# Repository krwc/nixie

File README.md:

# Another Nixie Clock, because why not?

When my journey into the world of electronics started, a friend of mine has shown me the
beautiful creations capable of presenting time using cold cathode tubes. Ever since then,
I wanted to create something similar, as it seemed like a pretty cool thing to do!

After some time, and two PCB revisions, the clock was actually useful, wasn't exploding,
and was looking quite neat overall to me.

# Safety

- The high voltage trace clearance is enforced to be 0.4mm
- There's a 1A slow fuse on the input
- There's a slow start mechanism implemented on the input, preventing high transient
  current during startup

Anyway, if you intend to use it, please do it on your own risk. Keep in mind, I'm not
a professional PCB designer, nor have a proper electrical education background.

# Acknolwedgements

- The power supply design is based on https://threeneurons.wordpress.com/nixie-power-supply/,
  and the datasheet of MC33063 itself. It is integrated into the main PCB.

- Wemos KiCad model was found somewhere on the internet, unfortunately I can't remember where
  exactly.

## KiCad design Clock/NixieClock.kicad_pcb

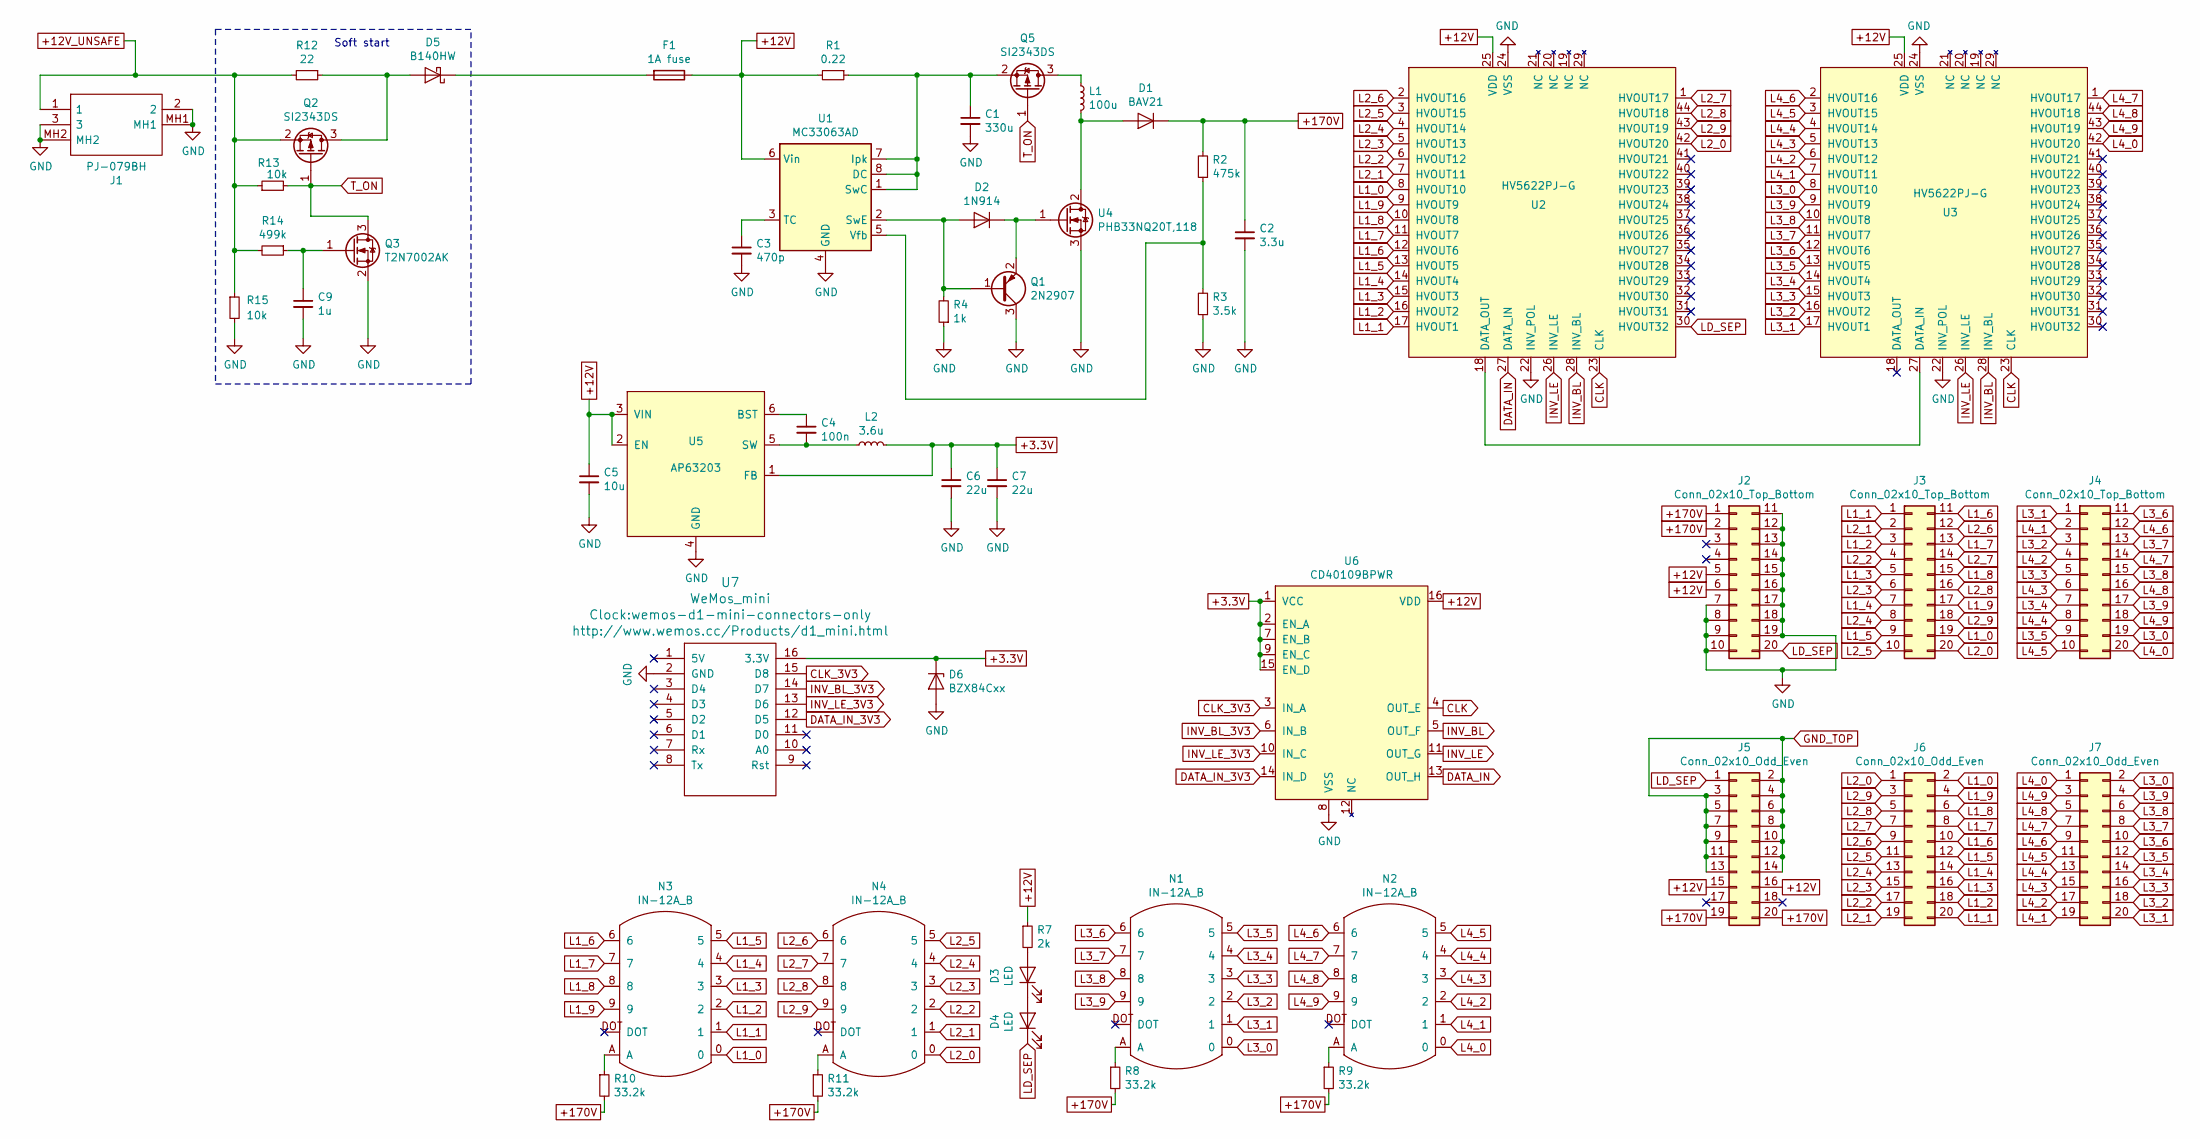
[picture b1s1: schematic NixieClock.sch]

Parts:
C1: 330u; C_Radial_D10.0mm_H20.0mm_P5.00mm
C2: 3.3u; C_Radial_D6.3mm_H11.0mm_P2.50mm
C3: 470p; C_0603_1608Metric
C4: 100n; C_0603_1608Metric_Pad1.05x0.95mm_HandSolder
C5: 10u; C_0805_2012Metric_Pad1.15x1.40mm_HandSolder
C6, C7: 22u; C_0805_2012Metric_Pad1.15x1.40mm_HandSolder
C9: 1u; C_0603_1608Metric_Pad1.05x0.95mm_HandSolder
D1: BAV21; D_SOD-323_HandSoldering
D2: 1N914; D_SOD-323_HandSoldering
D3, D4: LED; LED_D5.0mm_Clear
D5: B140HW; D_SOD-123
D6: BZX84Cxx; D_SOT-23_ANK
F1: 1A fuse; Fuse_1206_3216Metric_Pad1.42x1.75mm_HandSolder
J1: PJ-079BH; PJ079BH
J2, J3, J4: Conn_02x10_Top_Bottom; PinHeader_2x10_P2.54mm_Vertical
J5, J6, J7: Conn_02x10_Odd_Even; PinSocket_2x10_P2.54mm_Horizontal
L1: 100u; L_Bourns_SRR1210A
L2: 3.6u; SRN5040
N1, N2, N3, N4: IN-12A_B; IN12-A_B
Q1: 2N2907; SOT-23_Handsoldering
Q2, Q5: SI2343DS; SOT-23_Handsoldering
Q3: T2N7002AK; SOT-23_Handsoldering
R1: 0.22; R_1210_3225Metric_Pad1.42x2.65mm_HandSolder
R2: 475k; R_1206_3216Metric_Pad1.42x1.75mm_HandSolder
R3: 3.5k; R_1206_3216Metric_Pad1.42x1.75mm_HandSolder
R4: 1k; R_0603_1608Metric_Pad1.05x0.95mm_HandSolder
R7: 2k; R_0603_1608Metric_Pad1.05x0.95mm_HandSolder
R8, R9, R10, R11: 33.2k; R_1206_3216Metric_Pad1.42x1.75mm_HandSolder
R12: 22; R_2512_6332Metric_Pad1.52x3.35mm_HandSolder
R13, R15: 10k; R_0603_1608Metric_Pad1.05x0.95mm_HandSolder
R14: 499k; R_0603_1608Metric_Pad1.05x0.95mm_HandSolder
U1: MC33063AD; SOIC-8_3.9x4.9mm_P1.27mm
U2, U3: HV5622PJ-G; PLCC-44
U4: PHB33NQ20T,118; TO-263-3_TabPin2
U5: AP63203; TSOT-23-6
U6: CD40109BPWR; TSSOP-16_4.4x5mm_P0.65mm
U7: WeMos_mini; wemos-d1-mini-connectors-only

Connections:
+3.3V: C6.1, C7.1, D6.1 (K), L2.2, U5.1 (FB), U6.1 (VCC), U6.2 (EN_A), U6.7 (EN_B), U6.9 (EN_C), U6.15 (EN_D), U7.16 (3.3V)
+12V: C5.1, F1.1, J2.5, J2.6, J5.15, J5.16, R1.2, R7.1, U1.6 (Vin), U2.25 (VDD), U3.25 (VDD), U5.2 (EN), U5.3 (VIN), U6.16 (VDD)
+12V_UNSAFE: J1.1, Q2.2 (S), R12.2, R13.1, R14.2, R15.1
+170V: C2.1, D1.1 (K), J2.1, J2.2, J5.19, J5.20, R2.2, R8.2, R9.2, R10.2, R11.2
CLK: U2.23 (CLK), U3.23 (CLK), U6.4 (OUT_E)
CLK_3V3: U6.3 (IN_A), U7.15 (D8)
DATA_IN: U2.27 (DATA_IN), U6.13 (OUT_H)
DATA_IN_3V3: U6.14 (IN_D), U7.12 (D5)
GND: C1.2, C2.2, C3.2, C5.2, C6.2, C7.2, C9.2, D6.2 (A), J1.2, J1.3, J1.MH1, J1.MH2, J2.7, J2.8, J2.9, J2.10, J2.11, J2.12, J2.13, J2.14, J2.15, J2.16, J2.17, J2.18, J2.19, Q1.3 (C), Q3.2 (S), R3.1, R4.1, R15.2, U1.4 (GND), U2.22 (INV_POL), U2.24 (VSS), U3.22 (INV_POL), U3.24 (VSS), U4.3 (S), U5.4 (GND), U6.8 (VSS), U7.2 (GND)
GND_TOP: J5.2, J5.3, J5.4, J5.5, J5.6, J5.7, J5.8, J5.9, J5.10, J5.11, J5.12, J5.13, J5.14
INV_BL: U2.28 (INV_BL), U3.28 (INV_BL), U6.5 (OUT_F)
INV_BL_3V3: U6.6 (IN_B), U7.14 (D7)
INV_LE: U2.26 (INV_LE), U3.26 (INV_LE), U6.11 (OUT_G)
INV_LE_3V3: U6.10 (IN_C), U7.13 (D6)
L1_0: J3.19, J6.2, N3.0, U2.8 (HVOUT10)
L1_1: J3.1, J6.20, N3.1, U2.17 (HVOUT1)
L1_2: J3.3, J6.18, N3.2, U2.16 (HVOUT2)
L1_3: J3.5, J6.16, N3.3, U2.15 (HVOUT3)
L1_4: J3.7, J6.14, N3.4, U2.14 (HVOUT4)
L1_5: J3.9, J6.12, N3.5, U2.13 (HVOUT5)
L1_6: J3.11, J6.10, N3.6, U2.12 (HVOUT6)
L1_7: J3.13, J6.8, N3.7, U2.11 (HVOUT7)
L1_8: J3.15, J6.6, N3.8, U2.10 (HVOUT8)
L1_9: J3.17, J6.4, N3.9, U2.9 (HVOUT9)
L2_0: J3.20, J6.1, N4.0, U2.42 (HVOUT20)
L2_1: J3.2, J6.19, N4.1, U2.7 (HVOUT11)
L2_2: J3.4, J6.17, N4.2, U2.6 (HVOUT12)
L2_3: J3.6, J6.15, N4.3, U2.5 (HVOUT13)
L2_4: J3.8, J6.13, N4.4, U2.4 (HVOUT14)
L2_5: J3.10, J6.11, N4.5, U2.3 (HVOUT15)
L2_6: J3.12, J6.9, N4.6, U2.2 (HVOUT16)
L2_7: J3.14, J6.7, N4.7, U2.1 (HVOUT17)
L2_8: J3.16, J6.5, N4.8, U2.44 (HVOUT18)
L2_9: J3.18, J6.3, N4.9, U2.43 (HVOUT19)
L3_0: J4.19, J7.2, N1.0, U3.8 (HVOUT10)
L3_1: J4.1, J7.20, N1.1, U3.17 (HVOUT1)
L3_2: J4.3, J7.18, N1.2, U3.16 (HVOUT2)
L3_3: J4.5, J7.16, N1.3, U3.15 (HVOUT3)
L3_4: J4.7, J7.14, N1.4, U3.14 (HVOUT4)
L3_5: J4.9, J7.12, N1.5, U3.13 (HVOUT5)
L3_6: J4.11, J7.10, N1.6, U3.12 (HVOUT6)
L3_7: J4.13, J7.8, N1.7, U3.11 (HVOUT7)
L3_8: J4.15, J7.6, N1.8, U3.10 (HVOUT8)
L3_9: J4.17, J7.4, N1.9, U3.9 (HVOUT9)
L4_0: J4.20, J7.1, N2.0, U3.42 (HVOUT20)
L4_1: J4.2, J7.19, N2.1, U3.7 (HVOUT11)
L4_2: J4.4, J7.17, N2.2, U3.6 (HVOUT12)
L4_3: J4.6, J7.15, N2.3, U3.5 (HVOUT13)
L4_4: J4.8, J7.13, N2.4, U3.4 (HVOUT14)
L4_5: J4.10, J7.11, N2.5, U3.3 (HVOUT15)
L4_6: J4.12, J7.9, N2.6, U3.2 (HVOUT16)
L4_7: J4.14, J7.7, N2.7, U3.1 (HVOUT17)
L4_8: J4.16, J7.5, N2.8, U3.44 (HVOUT18)
L4_9: J4.18, J7.3, N2.9, U3.43 (HVOUT19)
LD_SEP: D4.1 (K), J2.20, J5.1, U2.30 (HVOUT32)
unnamed: C1.1, Q5.2 (S), R1.1, U1.1 (SwC), U1.7 (Ipk), U1.8 (DC)
unnamed: C3.1, U1.3 (TC)
unnamed: C4.1, U5.6 (BST)
unnamed: C4.2, L2.1, U5.5 (SW)
unnamed: C9.1, Q3.1 (G), R14.1
unnamed: D1.2 (A), L1.2, U4.2 (D)
unnamed: D2.1 (K), Q1.2 (E), U4.1 (G)
unnamed: D2.2 (A), Q1.1 (B), R4.2, U1.2 (SwE)
unnamed: D3.1 (K), D4.2 (A)
unnamed: D3.2 (A), R7.2
unnamed: D5.1 (K), F1.2
unnamed: D5.2 (A), Q2.3 (D), R12.1
unnamed: L1.1, Q5.3 (D)
unnamed: N1.A, R8.1
unnamed: N2.A, R9.1
unnamed: N3.A, R10.1
unnamed: N4.A, R11.1
unnamed: R2.1, R3.2, U1.5 (Vfb)
unnamed: U2.18 (DATA_OUT), U3.27 (DATA_IN)
T_ON: Q2.1 (G), Q3.3 (D), Q5.1 (G), R13.2

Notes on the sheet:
Soft start

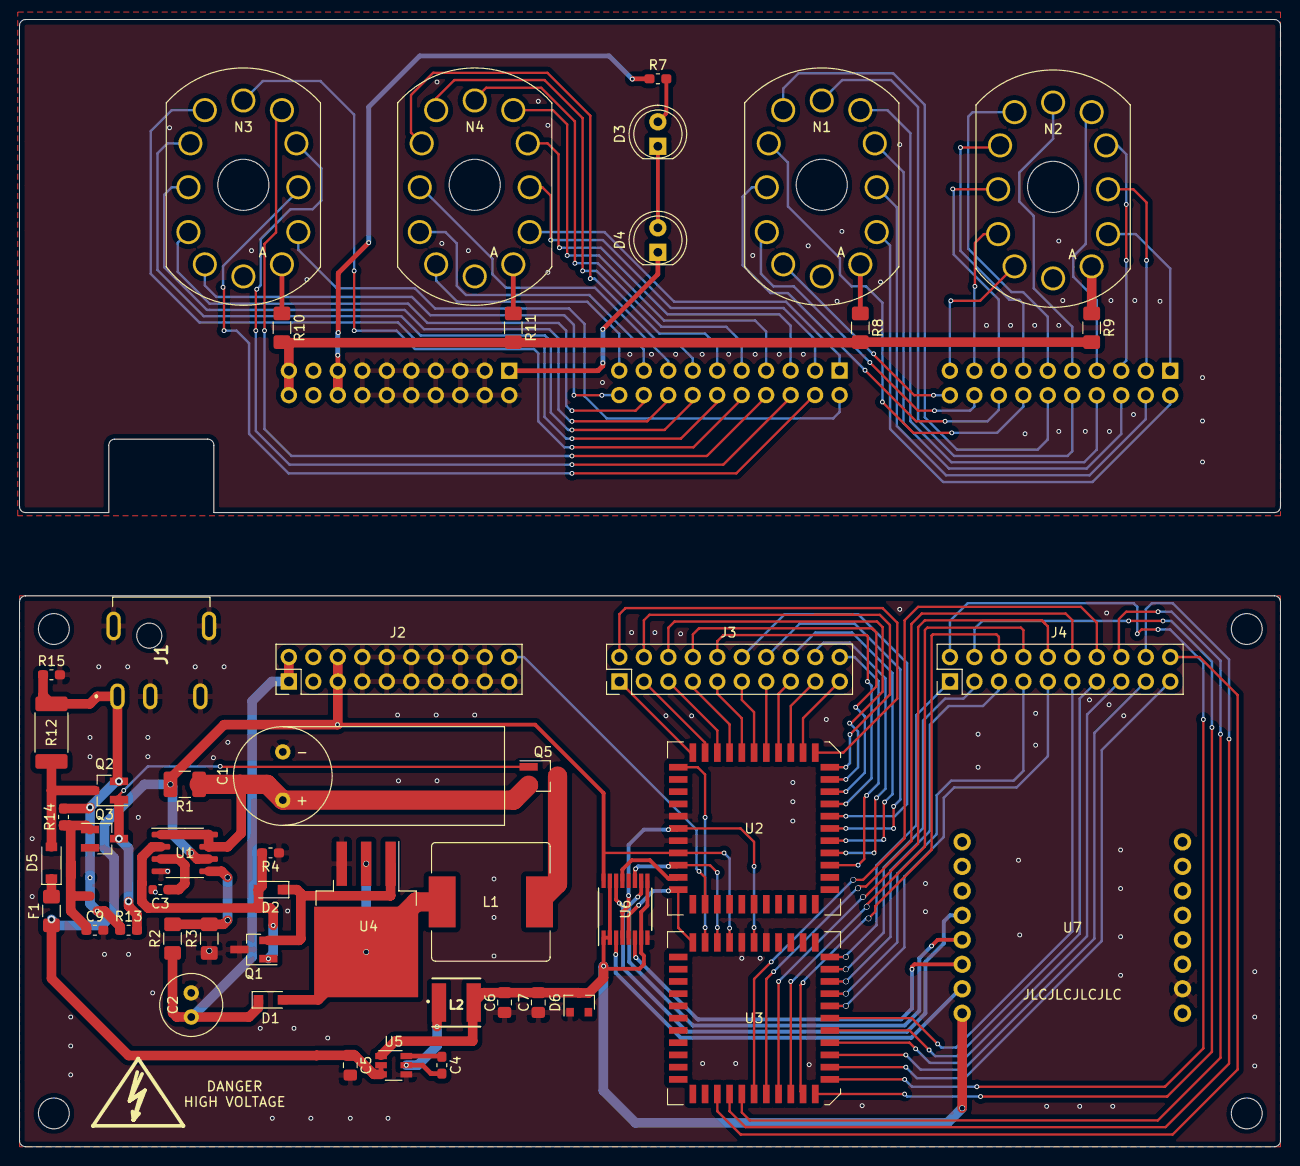
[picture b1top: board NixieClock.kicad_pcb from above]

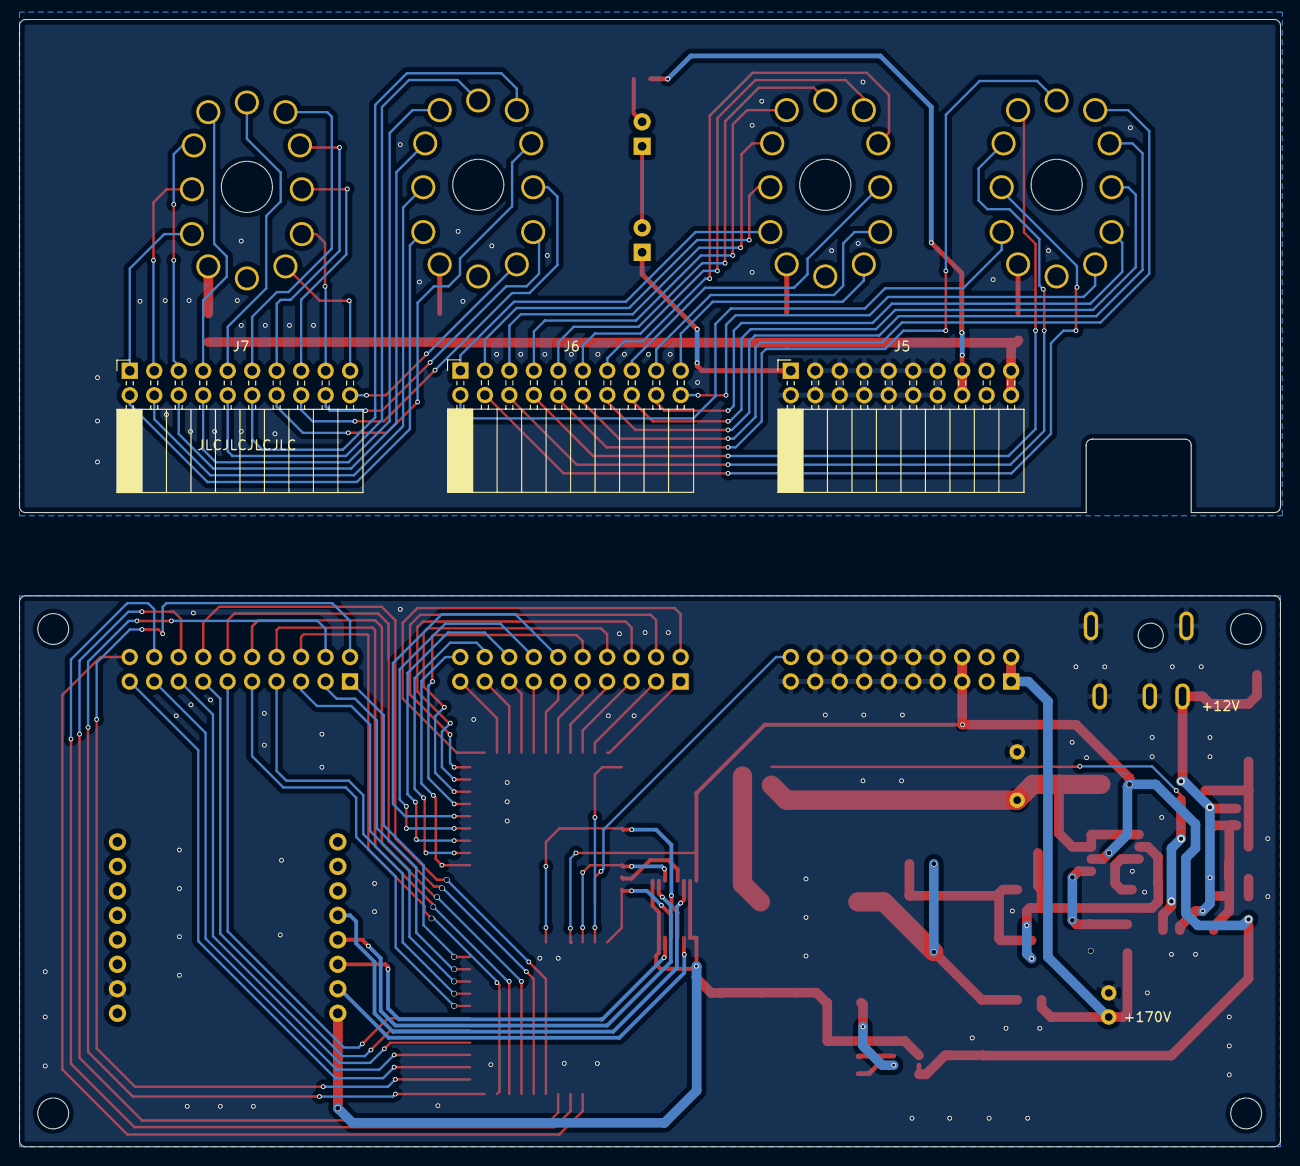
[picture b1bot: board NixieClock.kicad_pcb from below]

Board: 2 copper layers, 130.8 x 116.9 mm, 53 parts (3 on the bottom side), 75 nets.

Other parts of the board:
SYM1: SYM_Flash_Small; HighVoltage

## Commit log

2019-08-19 Nixie clock implementation.
2019-08-26 v2.0
2019-10-07 Add v2.0 plots
2019-10-07 Add firmware for esp8266
2020-01-02 Remove a "fast-discharge" transistor, as it was not operating as intended due to emitter-base breakdown. It was pretty much optional anyway.
2020-01-02 Add README.md
2020-01-02 Fix urls to pictures
2020-01-02 Fix wording
